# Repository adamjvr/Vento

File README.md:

# Vento
ARM Cortex M4F + WiFi+BLE + MPPT Solar Battery Powered module, mBed and Arduino Compatible hardware development
- ARM Cortex M4F 180MHZ STM32F446RET6
- ESP32 WiFi/BLE Dual Core SoC w/ PCB Antenna
- Bluetooth Classic
- Bluetooth Low Engergy (BLE)
- WiFi
- USB 2.0 Connectivity
- Plenty of GPIO
- PLenty of UART/I2C
- Lithium Ion Battery Power
- MPPT Solar battery charging
- USB bus power for desktop development
- Over the Air Programming
- Low power
- 2 Year Battery Life w/Single Cell Lithium Battery

Vento 0.1a KiCAD PCB

KiCAD PCB 3D Render
Top

Bottom

Vento 0.1a ESP3212 KiCAD PCB

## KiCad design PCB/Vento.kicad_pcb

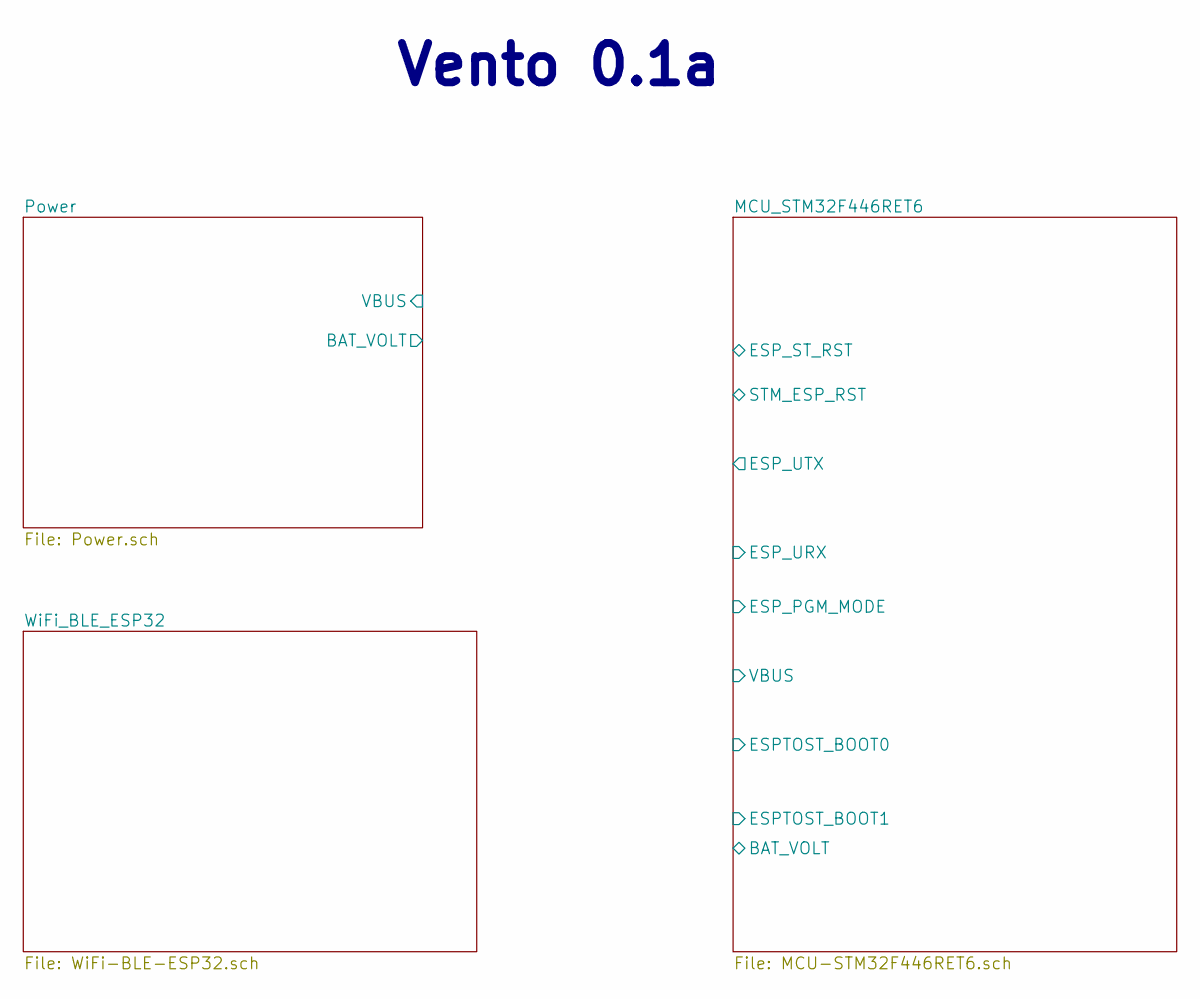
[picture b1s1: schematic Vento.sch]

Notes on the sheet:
Vento 0.1a

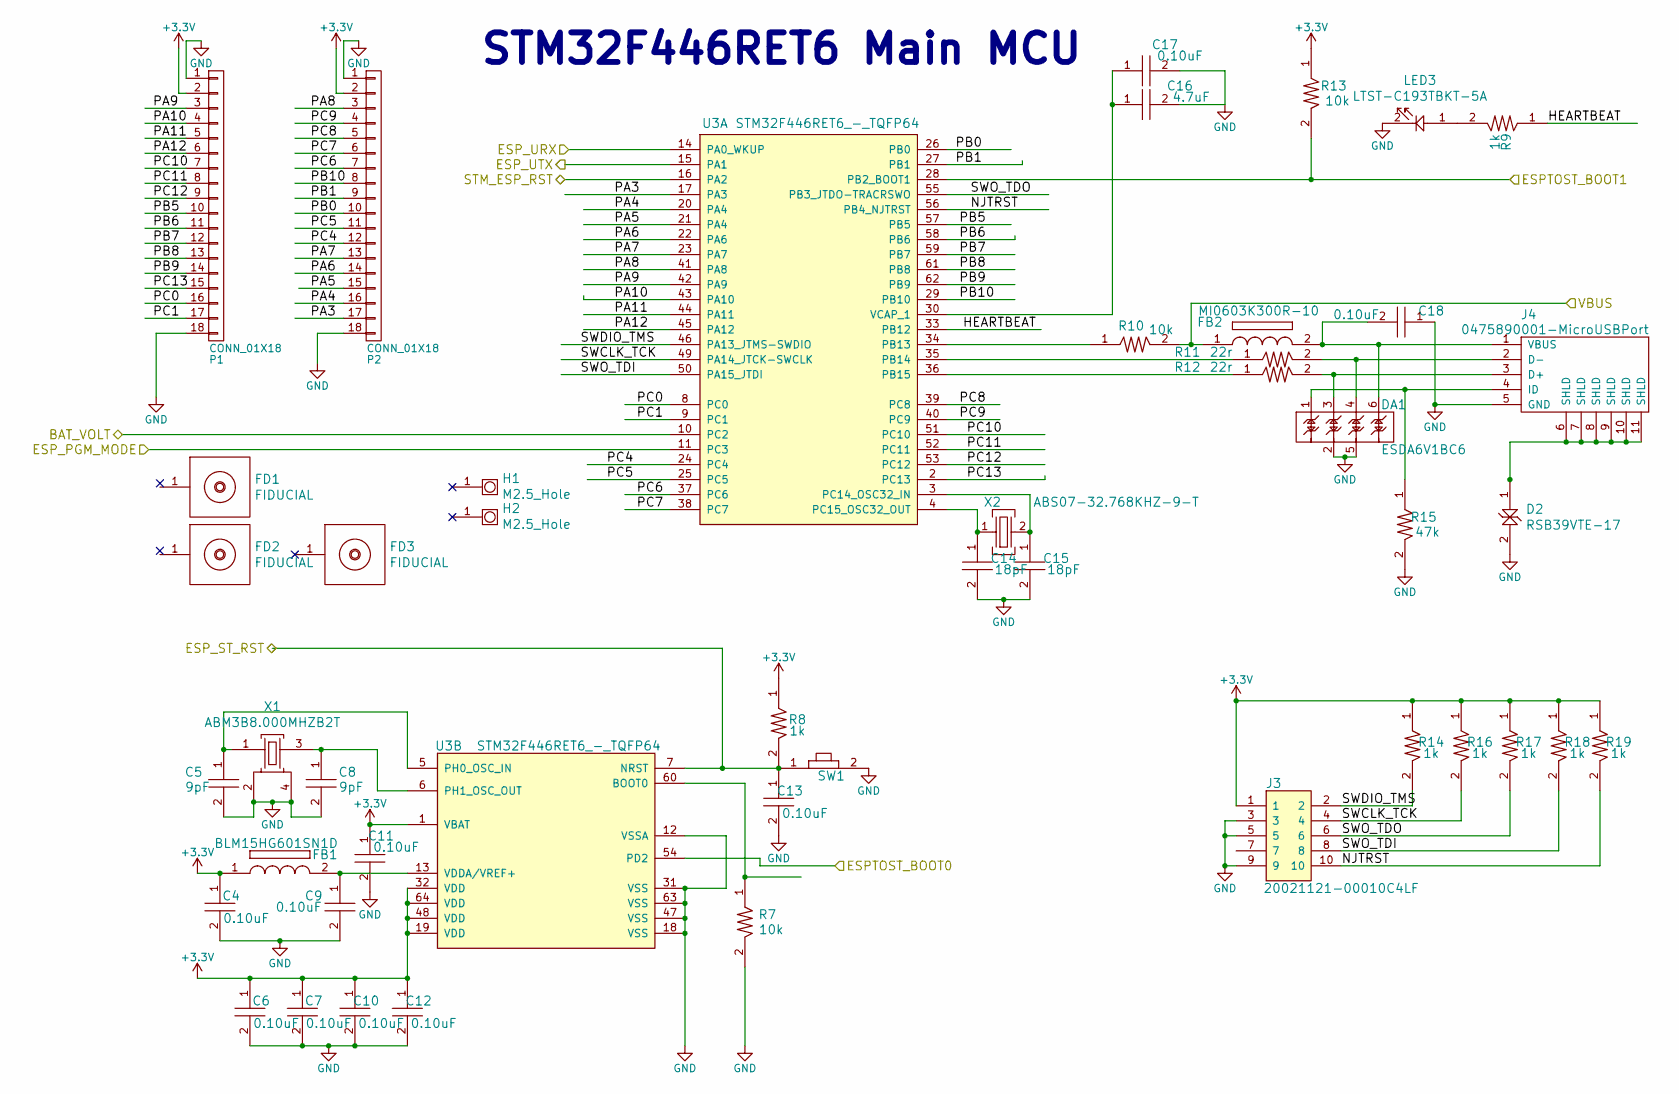
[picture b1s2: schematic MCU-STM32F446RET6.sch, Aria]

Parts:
C4, C6, C7, C9, C10, C11, C12, C13, C17, C18: CL05B104JP5NNNC; C0402; Tolerance 5%; Voltage 10V; MFR# CL05B104JP5NNNC
C5, C8: CL05C090CB5NNNC; C0402; Tolerance 0.25pF; Voltage 50V; MFR# CL05C090CB5NNNC
C14, C15: CL05C180GB5NCNC; C0402; Tolerance 2%; Voltage 50V; MFR# CL05C180GB5NCNC
C16: CL05A475KQ5NRNC; C0402; Tolerance 10%; Voltage 25V; MFR# CL05A475KQ5NRNC
D2: RSB39VTE-17; Tolerance N/A; Voltage 30V; MFR# RSB39VTE-17
DA1: ESDA6V1BC6; Tolerance N/A; Voltage 4V; MFR# ESDA6V1BC6
FB1: BLM15HG601SN1D; Tolerance N/A; Voltage N/A; MFR# BLM15HG601SN1D
FB2: MI0603K300R-10; Tolerance N/A; Voltage N/A; MFR# MI0603K300R-10
FD1, FD2, FD3: FIDUCIAL
H1, H2: M2.5_Hole; M2.5_HOLE
J3: 20021121-00010C4LF; Tolerance N/A; Voltage 200V MAX; MFR# 20021121-00010C4LF
J4: 0475890001-MicroUSBPort; 0475890001; Tolerance N/A; Voltage 5V; MFR# 0475890001
LED3: LTST-C193TBKT-5A; LED0603; Tolerance N/A; Voltage 2.8V Forward Voltage; MFR# LTST-C193TBKT-5A
P1, P2: CONN_01X18
R7, R10, R13: RC1005F103CS; R0402; Tolerance 1%; Voltage N/A; MFR# RC1005F103CS
R8, R9, R14, R16, R17, R18, R19: RC1005F102CS; R0402; Tolerance %; Voltage N/A; MFR# RC1005F102CS
R11, R12: CPF0402B22RE1; R0402; Tolerance 0.1%; Voltage N/A; MFR# CPF0402B22RE1
R15: RC1005J473CS; R0402; Tolerance 5%; Voltage N/A; MFR# RC1005J473CS
SW1: B3U-1000P; Tolerance %; Voltage 50V; MFR# B3U-1000P
U3: STM32F446RET6_-_TQFP64; STM32F446RET6; Tolerance N/A; Voltage 1.8-3.3V; MFR# STM32F446RET6
X1: ABM3B8.000MHZB2T; Tolerance N/A; Voltage 3.3V; MFR# ABM3B-8.000MHZ-B2-T
X2: ABS07-32.768KHZ-9-T; Tolerance ±20ppm; Voltage N/A; MFR# ABS07-32.768KHZ-9-T

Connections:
+3V3: C4.1, C6.1, C7.1, C10.1, C11.1, C12.1, FB1.1, J3.1, P1.2, P2.2, R8.1, R13.1, R14.1, R16.1, R17.1, R18.1, R19.1, U3.1 (VBAT), U3.19 (VDD), U3.32 (VDD), U3.48 (VDD), U3.64 (VDD); also elsewhere on the board
/MCU_STM32F446RET6/BAT_VOLT: U3.10 (PC2); also elsewhere on the board
/MCU_STM32F446RET6/ESPTOST_BOOT0: U3.54 (PD2); also elsewhere on the board
/MCU_STM32F446RET6/ESPTOST_BOOT1: R13.2, U3.28 (PB2_BOOT1); also elsewhere on the board
/MCU_STM32F446RET6/ESP_PGM_MODE: U3.11 (PC3); also elsewhere on the board
/MCU_STM32F446RET6/ESP_ST_RST: C13.1, R8.2, SW1.1, U3.7 (NRST); also elsewhere on the board
/MCU_STM32F446RET6/ESP_URX: U3.14 (PA0_WKUP); also elsewhere on the board
/MCU_STM32F446RET6/ESP_UTX: U3.15 (PA1); also elsewhere on the board
/MCU_STM32F446RET6/HEARTBEAT: R9.1, U3.33 (PB12)
/MCU_STM32F446RET6/NJTRST: J3.10, R19.2, U3.56 (PB4_NJTRST)
/MCU_STM32F446RET6/PA3: P2.17, U3.17 (PA3)
/MCU_STM32F446RET6/PA4: P2.16, U3.20 (PA4)
/MCU_STM32F446RET6/PA5: P2.15, U3.21 (PA4)
/MCU_STM32F446RET6/PA6: P2.14, U3.22 (PA6)
/MCU_STM32F446RET6/PA7: P2.13, U3.23 (PA7)
/MCU_STM32F446RET6/PA8: P2.3, U3.41 (PA8)
/MCU_STM32F446RET6/PA9: P1.3, U3.42 (PA9)
/MCU_STM32F446RET6/PA10: P1.4, U3.43 (PA10)
/MCU_STM32F446RET6/PA11: P1.5, U3.44 (PA11)
/MCU_STM32F446RET6/PA12: P1.6, U3.45 (PA12)
/MCU_STM32F446RET6/PB0: P2.10, U3.26 (PB0)
/MCU_STM32F446RET6/PB1: P2.9, U3.27 (PB1)
/MCU_STM32F446RET6/PB5: P1.10, U3.57 (PB5)
/MCU_STM32F446RET6/PB6: P1.11, U3.58 (PB6)
/MCU_STM32F446RET6/PB7: P1.12, U3.59 (PB7)
/MCU_STM32F446RET6/PB8: P1.13, U3.61 (PB8)
/MCU_STM32F446RET6/PB9: P1.14, U3.62 (PB9)
/MCU_STM32F446RET6/PB10: P2.8, U3.29 (PB10)
/MCU_STM32F446RET6/PC0: P1.16, U3.8 (PC0)
/MCU_STM32F446RET6/PC1: P1.17, U3.9 (PC1)
/MCU_STM32F446RET6/PC4: P2.12, U3.24 (PC4)
/MCU_STM32F446RET6/PC5: P2.11, U3.25 (PC5)
/MCU_STM32F446RET6/PC6: P2.7, U3.37 (PC6)
/MCU_STM32F446RET6/PC7: P2.6, U3.38 (PC7)
/MCU_STM32F446RET6/PC8: P2.5, U3.39 (PC8)
/MCU_STM32F446RET6/PC9: P2.4, U3.40 (PC9)
/MCU_STM32F446RET6/PC10: P1.7, U3.51 (PC10)
/MCU_STM32F446RET6/PC11: P1.8, U3.52 (PC11)
/MCU_STM32F446RET6/PC12: P1.9, U3.53 (PC12)
/MCU_STM32F446RET6/PC13: P1.15, U3.2 (PC13)
/MCU_STM32F446RET6/STM_ESP_RST: U3.16 (PA2); also elsewhere on the board
/MCU_STM32F446RET6/SWCLK_TCK: J3.4, R16.2, U3.49 (PA14_JTCK-SWCLK)
/MCU_STM32F446RET6/SWDIO_TMS: J3.2, R14.2, U3.46 (PA13_JTMS-SWDIO)
/MCU_STM32F446RET6/SWO_TDI: J3.8, R18.2, U3.50 (PA15_JTDI)
/MCU_STM32F446RET6/SWO_TDO: J3.6, R17.2, U3.55 (PB3_JTDO-TRACRSWO)
/MCU_STM32F446RET6/VBUS: FB2.1, R10.2; also elsewhere on the board
GND: C4.2, C5.2, C6.2, C7.2, C8.2, C9.2, C10.2, C11.2, C12.2, C13.2, C14.2, C15.2, C16.2, C17.2, C18.1, D2.2, DA1.2, DA1.5, J3.3, J3.5, J3.9, J4.5 (GND), LED3.2, P1.1, P1.18, P2.1, P2.18, R7.2, R15.2, SW1.2, U3.12 (VSSA), U3.18 (VSS), U3.31 (VSS), U3.47 (VSS), U3.63 (VSS), X1.2, X1.4; also elsewhere on the board
unnamed: C5.1, U3.5 (PH0_OSC_IN), X1.1
unnamed: C8.1, U3.6 (PH1_OSC_OUT), X1.3
unnamed: C9.1, FB1.2, U3.13 (VDDA/VREF+)
unnamed: C14.1, U3.4 (PC15_OSC32_OUT), X2.1
unnamed: C15.1, U3.3 (PC14_OSC32_IN), X2.2
unnamed: C16.1, C17.1, U3.30 (VCAP_1)
unnamed: C18.2, DA1.6, FB2.2, J4.1 (VBUS)
unnamed: D2.1, J4.6 (SHLD), J4.7 (SHLD), J4.8 (SHLD), J4.9 (SHLD), J4.10 (SHLD), J4.11 (SHLD)
unnamed: DA1.1, J4.4 (ID), R15.1
unnamed: DA1.3, J4.3 (D+), R12.2
unnamed: DA1.4, J4.2 (D-), R11.2
unnamed: LED3.1, R9.2
unnamed: R7.1, U3.60 (BOOT0)
unnamed: R10.1, U3.34 (PB13)
unnamed: R11.1, U3.35 (PB14)
unnamed: R12.1, U3.36 (PB15)

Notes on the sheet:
STM32F446RET6 Main MCU

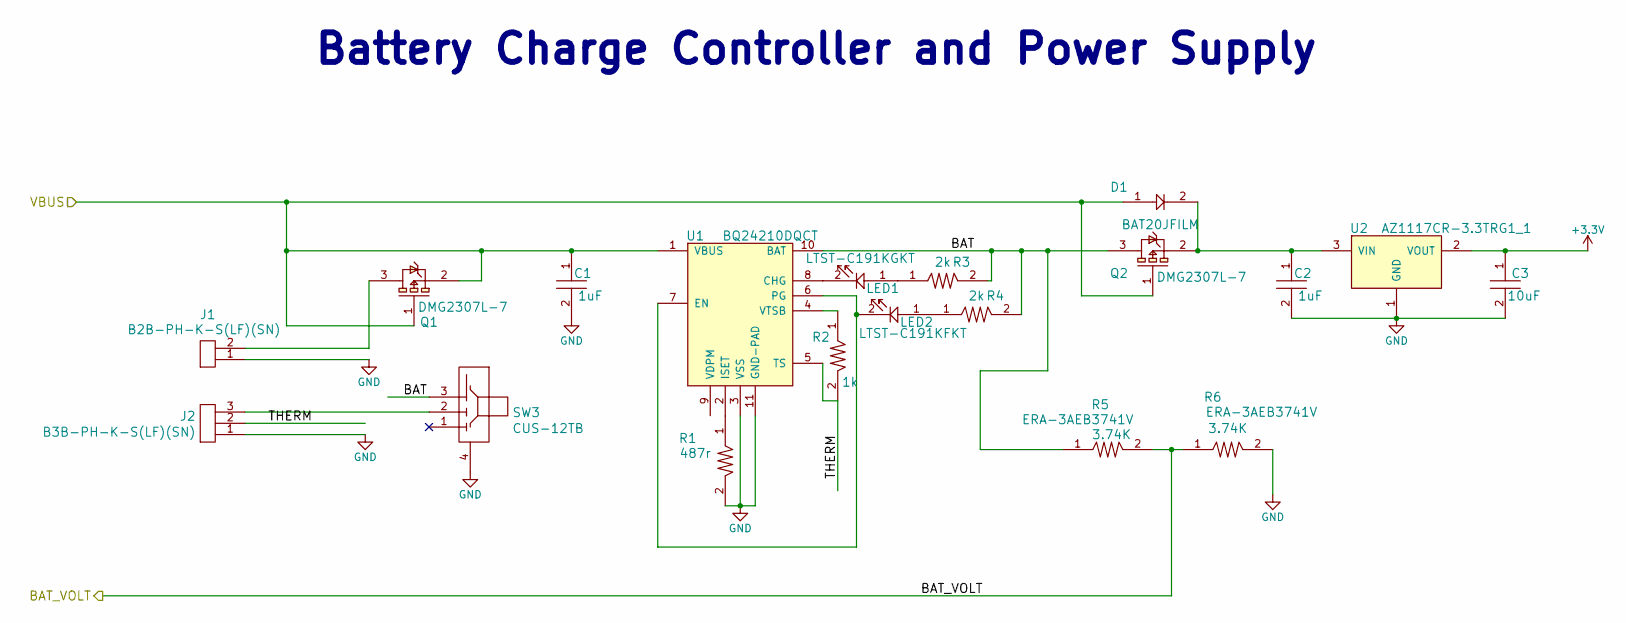
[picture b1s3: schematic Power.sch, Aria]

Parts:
C1, C2: CL05A105KA5NQNC; C0402; Tolerance 10%; Voltage 25V; MFR# CL05A105KA5NQNC
C3: CL10A106KQ8NNNC; C0603; Tolerance 10%; Voltage 6.3V; MFR# CL10A106KQ8NNNC
D1: BAT20JFILM; Tolerance N/A; Voltage N/A; MFR# BAT20JFILM
J1: B2B-PH-K-S(LF)(SN); Tolerance N/A; Voltage N/A; MFR# B2B-PH-K-S(LF)(SN)
J2: B3B-PH-K-S(LF)(SN); Tolerance N/A; Voltage N/A; MFR# B3B-PH-K-S(LF)(SN)
LED1: LTST-C191KGKT; LED0603; Tolerance N/A; Voltage N/A; MFR# LTST-C191KGKT
LED2: LTST-C191KFKT; LED0603; Tolerance N/A; Voltage N/A; MFR# LTST-C191KFKT
Q1, Q2: DMG2307L-7; Tolerance N/A; Voltage 30V; MFR# DMG2307L-7
R1: RC1005F4870CS; R0402; Tolerance 1%; Voltage N/A; MFR# RC1005F4870CS
R2: RC1005F102CS; R0402; Tolerance %; Voltage N/A; MFR# RC1005F102CS
R3, R4: RC1608J202CS; R0603; Tolerance 1%; Voltage N/A; MFR# RC1608F202CS
R5, R6: ERA-3AEB3741V; R0603; Tolerance 1%; Voltage N/A; MFR# ERA-3AEB3741V
SW3: CUS-12TB; Tolerance N/A; Voltage 50V 100mA; MFR# CUS-12TB
U1: BQ24210DQCT; BQ24210; Tolerance N/A; Voltage 3.5-18VDC; MFR# BQ24210DQCT
U2: AZ1117CR-3.3TRG1_1; AZ1117CR-3.3TRG1; Tolerance N/A; Voltage 3.7V input 3.3V Output; MFR# AZ1117CR-3.3TRG1

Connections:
+3V3: C3.1, U2.2 (VOUT); also elsewhere on the board
/MCU_STM32F446RET6/BAT_VOLT: R5.2, R6.1; also elsewhere on the board
/MCU_STM32F446RET6/VBUS: C1.1, D1.1, Q1.1, Q1.2, Q2.1, U1.1 (VBUS); also elsewhere on the board
/Power/BAT: Q2.3, R3.2, R4.2, R5.1, SW3.3, U1.10 (BAT)
/Power/THERM: J2.2, R2.2, U1.5 (TS)
GND: C1.2, C2.2, C3.2, J1.1, J2.1, R1.2, R6.2, SW3.4, U1.3 (VSS), U1.11 (GND-PAD), U2.1 (GND); also elsewhere on the board
unnamed: C2.1, D1.2, Q2.2, U2.3 (VIN)
unnamed: J1.2, Q1.3
unnamed: J2.3, SW3.2
unnamed: LED1.1, R3.1
unnamed: LED1.2, U1.8 (CHG)
unnamed: LED2.1, R4.1
unnamed: LED2.2, U1.6 (PG), U1.7 (EN)
unnamed: R1.1, U1.2 (ISET)
unnamed: R2.1, U1.4 (VTSB)

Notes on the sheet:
Battery Charge Controller and Power Supply

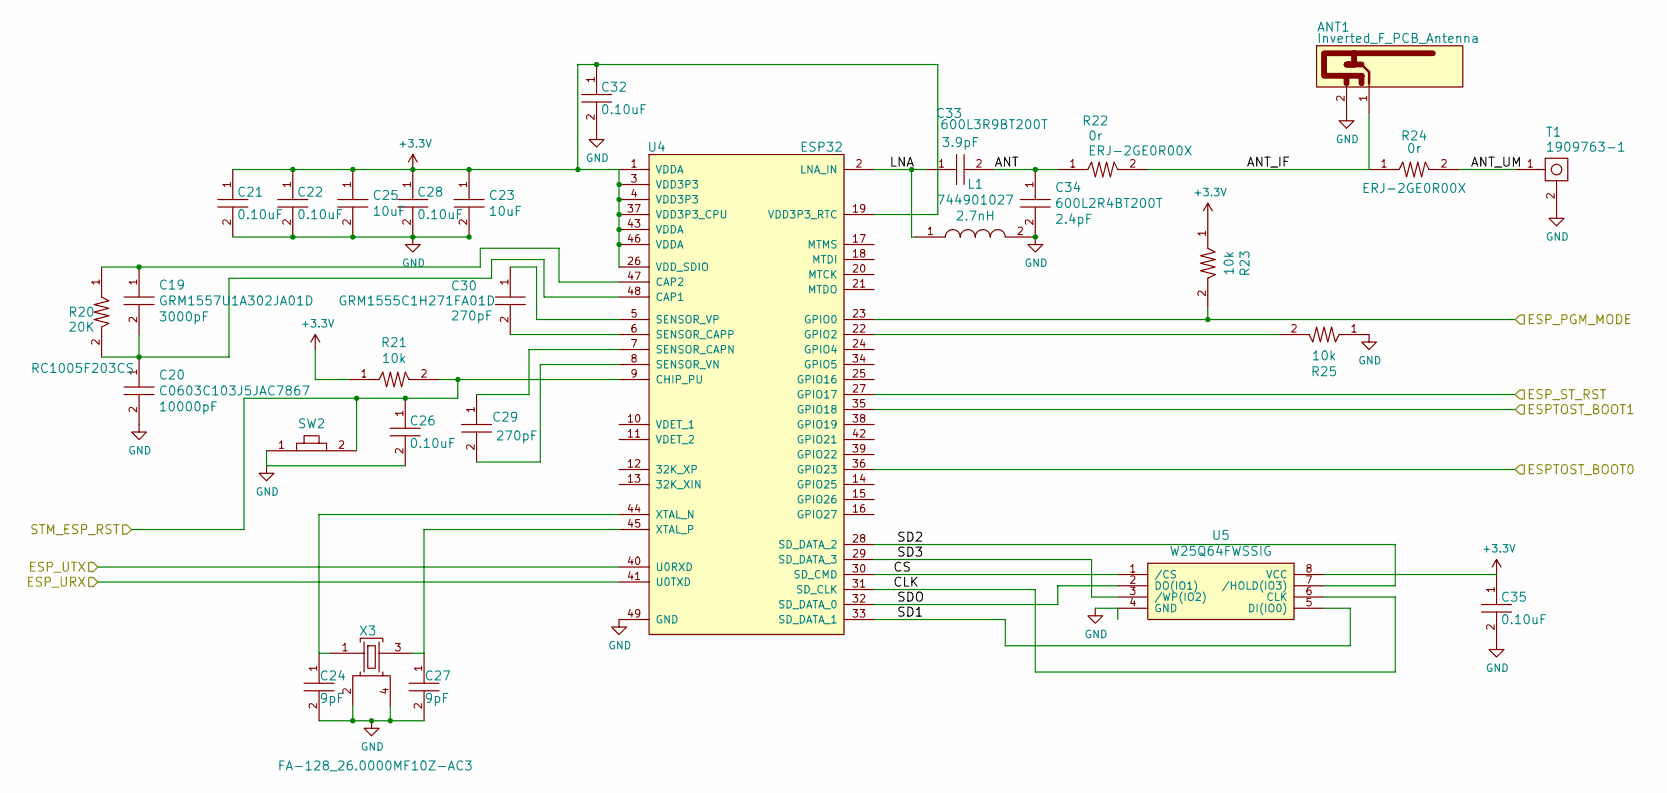
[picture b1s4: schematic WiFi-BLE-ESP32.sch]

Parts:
ANT1: Inverted_F_PCB_Antenna; PCB_IF_ANT_2.4G
C19: GRM1557U1A302JA01D; C0402; Tolerance 0.1pF; Voltage 10V; MFR# GRM1557U1A302JA01D
C20: C0603C103J5JAC7867; C0603; Tolerance 5%; Voltage 50V; MFR# C0603C103J5JAC7867
C21, C22, C26, C28, C32, C35: CL05B104JP5NNNC; C0402; Tolerance 5%; Voltage 10V; MFR# CL05B104JP5NNNC
C23, C25: CL10A106KQ8NNNC; C0603; Tolerance 10%; Voltage 6.3V; MFR# CL10A106KQ8NNNC
C24, C27: CL05C090CB5NNNC; C0402; Tolerance 0.25pF; Voltage 50V; MFR# CL05C090CB5NNNC
C29, C30: GRM1555C1H271FA01D; C0402; Tolerance 270pF; Voltage 50V; MFR# GRM1557U1A302JA01D
C33: 600L3R9BT200T; C0402; Tolerance 0.1pF; Voltage 200V; MFR# 600L3R9BT200T
C34: 600L2R4BT200T; C0402; Tolerance 2.4pF; Voltage 200V; MFR# 600L2R4BT200T
L1: 744901027; BLM15HG601SN1D; Tolerance 0.1nH; Voltage N/A; MFR# 744901027
R20: RC1005F203CS; R0402; Tolerance 1%; Voltage N/A; MFR# RC1005F103CS
R21, R23, R25: RC1005F103CS; R0402; Tolerance 1%; Voltage N/A; MFR# RC1005F103CS
R22, R24: ERJ-2GE0R00X; R0402; Tolerance %; Voltage N/A; MFR# ERJ-2GE0R00X
SW2: B3U-1000P; Tolerance %; Voltage 50V; MFR# B3U-1000P
T1: 1909763-1; Tolerance N/A; Voltage N/A; MFR# 1909763-1
U4: ESP32
U5: W25Q64FWSSIG; Tolerance N/A; Voltage 3.3V; MFR# W25Q64FWSSIG
X3: FA-128_26.0000MF10Z-AC3; Tolerance N/A; Voltage 3.3V; MFR# FA-128 26.0000MF10Z-AC3

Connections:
+3V3: C21.1, C22.1, C23.1, C25.1, C28.1, C32.1, C35.1, R21.1, R23.1, U4.1 (VDDA), U4.3 (VDD3P3), U4.4 (VDD3P3), U4.19 (VDD3P3_RTC), U4.26 (VDD_SDIO), U4.37 (VDD3P3_CPU), U4.43 (VDDA), U4.46 (VDDA), U5.8 (VCC); also elsewhere on the board
/MCU_STM32F446RET6/ESPTOST_BOOT0: U4.36 (GPIO23); also elsewhere on the board
/MCU_STM32F446RET6/ESPTOST_BOOT1: U4.35 (GPIO18); also elsewhere on the board
/MCU_STM32F446RET6/ESP_PGM_MODE: R23.2, U4.23 (GPIO0); also elsewhere on the board
/MCU_STM32F446RET6/ESP_ST_RST: U4.27 (GPIO17); also elsewhere on the board
/MCU_STM32F446RET6/ESP_URX: U4.41 (U0TXD); also elsewhere on the board
/MCU_STM32F446RET6/ESP_UTX: U4.40 (U0RXD); also elsewhere on the board
/MCU_STM32F446RET6/STM_ESP_RST: C26.1, R21.2, SW2.2, U4.9 (CHIP_PU); also elsewhere on the board
/WiFi_BLE_ESP32/ANT: C33.2, C34.1, R22.1
/WiFi_BLE_ESP32/ANT_IF: ANT1.1, R22.2, R24.1
/WiFi_BLE_ESP32/ANT_UM: R24.2, T1.1
/WiFi_BLE_ESP32/CLK: U4.31 (SD_CLK), U5.6 (CLK)
/WiFi_BLE_ESP32/CS: U4.30 (SD_CMD), U5.1 (/CS)
/WiFi_BLE_ESP32/LNA: C33.1, L1.1, U4.2 (LNA_IN)
/WiFi_BLE_ESP32/SD1: U4.33 (SD_DATA_1), U5.5 (DI(IO0))
/WiFi_BLE_ESP32/SD2: U4.28 (SD_DATA_2), U5.7 (/HOLD(IO3))
/WiFi_BLE_ESP32/SD3: U4.29 (SD_DATA_3), U5.3 (/WP(IO2))
/WiFi_BLE_ESP32/SDO: U4.32 (SD_DATA_0), U5.2 (DO(IO1))
GND: ANT1.2, C20.2, C21.2, C22.2, C23.2, C24.2, C25.2, C26.2, C27.2, C28.2, C32.2, C34.2, C35.2, L1.2, R25.1, SW2.1, T1.2, U4.49 (GND), U5.4 (GND), X3.2, X3.4; also elsewhere on the board
unnamed: C19.1, R20.1, U4.47 (CAP2)
unnamed: C19.2, C20.1, R20.2, U4.48 (CAP1)
unnamed: C24.1, U4.44 (XTAL_N), X3.1
unnamed: C27.1, U4.45 (XTAL_P), X3.3
unnamed: C29.1, U4.7 (SENSOR_CAPN)
unnamed: C29.2, U4.8 (SENSOR_VN)
unnamed: C30.1, U4.5 (SENSOR_VP)
unnamed: C30.2, U4.6 (SENSOR_CAPP)
unnamed: R25.2, U4.22 (GPIO2)

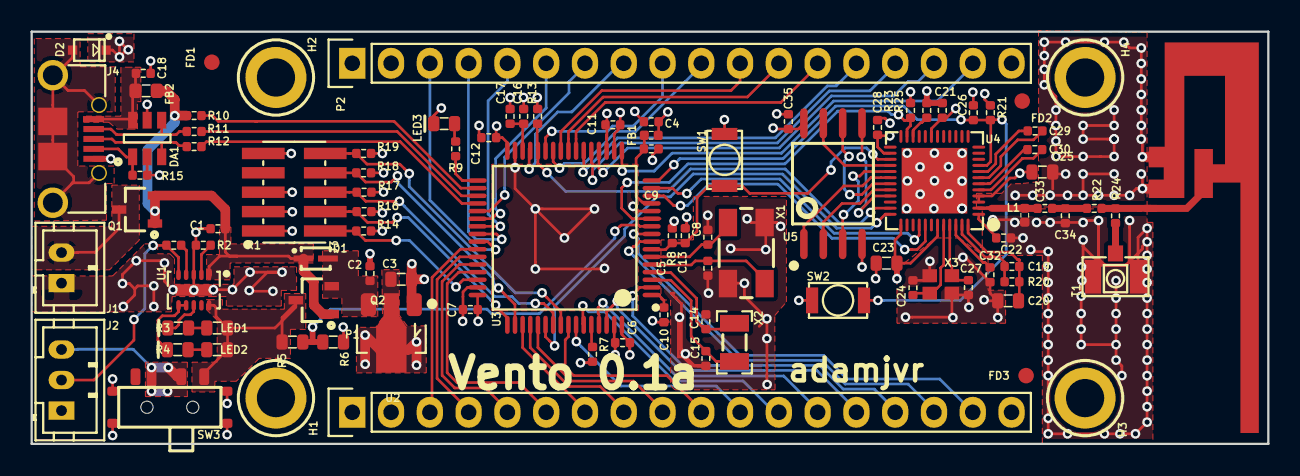
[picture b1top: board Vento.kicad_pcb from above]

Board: 4 copper layers, 81.0 x 27.0 mm, 96 parts (0 on the bottom side), 93 nets.

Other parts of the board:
H3, H4: M2.5_Hole; M2.5_HOLE

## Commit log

2016-09-27 Simple Specs
    Simple specs added to readme
2016-09-27 Schematic Development
    Schematic development still underway. Working on ESP32 section.
2016-09-29 License
    CERN Open Hardware License Added
2016-10-14 Schematic Done, Board Underway
    Schematic completed. STM32 section upated from Aria project schematic,
    ESP32 schematic completed with the help of reference schematic.
    Datasheets for componens used also added. The PCB is near complete, Aria
    was improted and modifed to speed up the process. More to come!
2016-10-14 Progress
    Headers routed, going to switch SPI flash on ESP32 circuit to SOIC model
    for simpler routing.
2016-10-14 PCB
    PCB done
2016-10-16 Tweaking and ESP3212 version
    Continuing to tweak the PCB, for optimal RF performance, thinking about
    capping either the RF section of the MCU+RF entirely. Also made an
    ESP3212 module version, both will be built at the same time when the
    time comes.
2016-10-18 Tweaks, DRC cleared, images, readme
    Tweaked both designs according to the dev board scheamtics provided by
    Espressif in the datasheets folder. Cleared both boards of DRC
    violations, added new images and updated the readme.
2016-10-18 Readme
    Updated error in image directory lines of readme markdown.
2016-10-18 Readme again
    Again more markdown errors fixed sheesh
2016-10-18 Added to Readme
    Added to the Readme
2016-10-18 Changes
    more readme changes
2016-10-27 On/Off And Cleanup
    Onoff Switch added, PCB extended 1mm to accomodated everything. routing
    and traes cleaned up. Heat sinking ground pours added to the BQ chip
2016-10-29 New Power Topology
    LDO swapped for one with a shutdown enable from Microchip. On/Off
    switchnow toggles the shutdown enable from the new LDO.
